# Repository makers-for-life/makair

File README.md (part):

MakAir — Covid-19 Ventilator
=====

Mass-producible open-source Covid-19 ARDS ventilator. Aims at helping hospitals cope with a possible shortage of professional ventilators during the outbreak. Worldwide.

**Makair ventilator is the world's first open-source ventilator tested with success on human patients** with ongoing clinical trials in France.

We are a distributed team of 200+ contributors (engineering, medical, regulatory, etc.), mostly spread through France. Makers, developers, university teachers, researchers and medical teams collaborated on this project. Our testing & assembly operations are located in France.

As to ensure international outreach, we made sure that contents required to build your own MakAir ventilator are available in English. The MakAir project has [a website of its own](https://makair.life/).

If you're new there, please read the explanations below. _Your contributions are much welcome!_

---

**Quick introduction video:**

<p align="center">
  
</p>

---

# Abstract

Roughly, the idea is as follows: as of April 2020 and due to the Covid-19 pandemic, hospitals throughout the world may start lacking mechanical artificial ventilators. We built a pump, and a valve system (controlled by electronics). This way, the breathing cycle can be enforced by proper air routing through the valve system.

Our ventilator is able to handle pressure-controlled breathing, stabilized using a [PID controller](https://en.wikipedia.org/wiki/PID_controller) in the software.

In order to ensure a proper breathing cycle (inhale + exhale), multiple valves need to be connected together to form a circuit. Their motors need to be controlled in harmony so that the air routing between each valve unit is consistent.

This project provides all the parts required to build a good-enough [ARDS](https://en.wikipedia.org/wiki/Acute_respiratory_distress_syndrome) ventilator from mass-produced components. We provide all the required mechanical parts, electronics designs & boards, and firmwares. This ventilator can be 3D-printed and ran on an Arduino board (the maker way), though we **highly advise** that you work with industrial processes as to mold medical-grade plastic parts and assemble the whole ventilator (this would be required for the built ventilator to pass all medical certifications).

We target a per-unit cost well under 500 EUR, which could easily be shrunk down to 200 EUR or even 100 EUR per ventilator given proper economies of scale, as well as choices of cheaper on-the-shelf components (eg. servomotors).

Features include:

- Pressure controlled ventilation (sedated / intubated patients)
- Volume controlled ventilation (sedated / intubated patients)
- BiPap ventilation (non sedated patients with oxygen mask)
- 4 hours battery life
- Medical-grade alarms
- High flow turbine (up to 100 L/min)
- Up to 15 L/min oxygen
- Fault tolerant design
- Designed to be used continuously and intensively during 30 days

MakAir ventilator has been tested by independent researchers and studies found that it can compare with expensive hospital reanimation ventilators (less than 5% error on target pressures and volumes).

Mechanically-speaking, the overall system is composed of sub-components that can be plugged together and wired to form an air circuit, namely:

- **Air pump** (called "Blower");
- **Air pump casing fit** (called "Blower Holder");
- **Valve system** (called "Pressure Valve");
- **Oxygen Mixer valve** (called "Oxygen Mixer");
- **Air filter casing (patient variant)** (called "Patient Filter Box");
- **Air filter casing (machine variant)** (called "Machine Filter Box"; intake + outtake);
- **Connectors** (called "Pneumatic Connectors");
- **Fan support** (called "Fan Holder");

All those components are fitted in box (ie. a casing) that we designed:

- **Housing container** (called "Casing");

---

# Designs

## MakAir Standard (Current Design)

## MakAir Mini (Experimental Design)

---

# ⚠️ Warning Notices

**A few important words before you start:**

1. Though 3D-printing (FDM and SLA) can be used to build your own ventilator — this will definitely not scale well to mass-produce MakAir ventilators, and parts might be brittle or leak air. Please work with proper industrial methods and processes if you want to build your own MakAir ventilators.

2. As ARDS patients are sedated, their breathing cycle is forced by mechanical ventilation, while they are intubated. A failing ventilator (due to bad mechanics, pneumatics or software) could kill the patient (O2 desaturation), or permanently damage their lung alveoli (overpressure). It is critical that any self-built MakAir ventilator is tested against a lung simulator system (eg. [ASL 5000](https://www.ingmarmed.com/product/asl-5000-breathing-simulator/)), and validated by medical experts.

3. Medical-grade plastic should be used to produce ventilators, and any kind of grease or adhesive chemicals must be avoided in the ventilator. The ventilators should be produced in a [cleanroom](https://en.wikipedia.org/wiki/Cleanroom) as to avoid dust & germ contaminations.

4. The pneumatic circuit should be thoroughly tested for leaks and its ability to withstand elevated positive air pressure. Joints should be used where relevant, and medical-grade flexible pipes should be used between components.

5. While the MakAir ventilators produced on-site in France were validated by a medical & engineering board, you should independantly seek validation of the MakAir ventilators that you produce; as your assembly methods or parts may vary with ours.

_MakAir and Makers For Life should not be held resposible — at any time, for harm caused to human life (eg. lung damage or loss of life). By building your own MakAir, you are held responsible for its safety validations & use._

# Projects

As the MakAir ventilator project grew up to be quite large, it is split up in sub-repositories (eg. firmware, PCB designs, etc.).

**Software:**

* **[makair-firmware](https://github.com/makers-for-life/makair-firmware)**: The firmware software source code and builds, that runs on the motherboard;
* **[makair-control-ui](https://github.com/makers-for-life/makair-control-ui)**: The control user interface, that shows realtime graphs of the ventilator while running, on a LCD display;
* **[makair-telemetry](https://github.com/makers-for-life/makair-telemetry)**: The telemetry library (and CLI tool), used as a protocol bridge between the Firmware and Control UI;

**Electronics:**

* **[makair-motherboard](https://github.com/makers-for-life/makair-motherboard)**: The motherboard electronics and PCB design;
* **[makair-boards](https://github.com/makers-for-life/makair-boards)**: Other boards PCB design (smaller control boards);

**Mechanics:**

* **[makair-parts](https://github.com/makers-for-life/makair-parts)**: The mechanical parts that can be 3D-printed and assembled to build the pneumatic circuit;
* **[makair-casing](https://github.com/makers-for-life/makair-casing)**: The MakAir casing which houses all electronics and pneumatics;

**Misc.:**

* **[makair-files](https://github.com/makers-for-life/makair-files)**: Large files, eg. the control UI system image that can be readily flashed and used;
* **[makair-simulator](https://github.com/makers-for-life/makair-simulator)**: The MakAir hardware simulator, that let us run a simulated firmware instance on a computer (for development purposes, ie. not used on ventilator units);
* **[makair-simulator-web](https://github.com/makers-for-life/makair-simulator-web)**: The Web version of the MakAir hardware simulator, that let us run a simulated firmware instance in a Web browser (for development purposes, ie. not used on ventilator units);

# How To Build?

This section aims at introducing you on how to manufacture your own MakAir — _the 3D-printed way_. In other words, we will explain there how to build a DIY MakAir using on-the-shelf parts and 3D printers.

## 1️⃣ Print all the parts

In order to 3D-print your MakAir, please first ensure you have access to a [SLS](https://en.wikipedia.org/wiki/Selective_laser_sintering) 3D printer at best (eg. [HP Multi Jet Fusion](https://www8.hp.com/us/en/printers/3d-printers/products/multi-jet-technology.html)), or otherwise a [SLA](https://en.wikipedia.org/wiki/Stereolithography) printer (eg. [Formlabs Form 3](https://formlabs.com/3d-printers/form-3/)). If you want to use a [FDM](https://en.wikipedia.org/wiki/Fused_filament_fabrication) printer (eg. [MakerBot Method](https://www.makerbot.com/3d-printers/method/)), please note that some precise parts have been optimized for SLA or SLS printing. Some parts may not print well using FDM printers, even on decent hardware.

**👉 To sum up:** at best, use a SLS metal printer, else, use a SLA resin printer. If you do not have access to either of these, you may fallback on a FDM filament printer (using [PLA](https://en.wikipedia.org/wiki/Polylactic_acid) or [ABS](https://en.wikipedia.org/wiki/Acrylonitrile_butadiene_styrene) filaments).

### 1. Parts

You can find a list of all parts that should be 3D-printed, as well as the number of parts that should be printed for each one (pick the last active version for each part):

- 1 x **Blower** — Print [all STL parts](https://github.com/makers-for-life/makair-parts/tree/master/src/blower/printing/stl) using the same printer (SLA or SLS; FDM discouraged; 50 microns minimum);
- 2 x **Pressure Valve** — Print [all STL parts](https://github.com/makers-for-life/makair-parts/tree/master/src/pressure-valve/printing/stl) using the same printer (SLA, SLS or FDM; 200 microns minimum);
- 1 x **Oxygen Mixer** — Print [the STL part](https://github.com/makers-for-life/makair-parts/tree/master/src/oxygen-mixer/printing/stl) (SLA or SLS; FDM discouraged; 100 microns minimum);
- 1 x **Patient Filter Box** — Print [all STL parts](https://github.com/makers-for-life/makair-parts/tree/master/src/patient-filter-box/printing/stl) using the same printer (SLA, SLS or FDM; 100 microns minimum);
- 1 x **Machine Filter Box (Intake)** — Print [all STL parts](https://github.com/makers-for-life/makair-parts/tree/master/src/machine-filter-box/printing/stl) using the same printer, make sure that you pick the proper sub-part (SLA or SLS; FDM discouraged; 100 microns minimum);
- 1 x **Machine Filter Box (Outtake)** — Print [all STL parts](https://github.com/makers-for-life/makair-parts/tree/master/src/machine-filter-box/printing/stl) using the same printer, make sure that you pick the proper sub-part (SLA or SLS; FDM discouraged; 100 microns minimum);
- 1 x **Pneumatic Connectors (Blower)** — Print [the STL part](https://github.com/makers-for-life/makair-parts/tree/master/src/pneumatic-connectors/printing/stl) using the same printer, make sure that you pick the proper sub-part (SLA or SLS; FDM discouraged; 100 microns minimum);
- 1 x **Pneumatic Connectors (O2)** — Print [the STL part](https://github.com/makers-for-life/makair-parts/tree/master/src/pneumatic-connectors/printing/stl) using the same printer, make sure that you pick the proper sub-part (SLA or SLS; FDM discouraged; 100 microns minimum);
- 1 x **Pneumatic Connectors (No Pressure)** — Print [the STL part](https://github.com/makers-for-life/makair-parts/tree/master/src/pneumatic-connectors/printing/stl) using the same printer, make sure that you pick the proper sub-part (SLA or SLS; FDM discouraged; 100 microns minimum);
- 1 x **Pneumatic Connectors (Pressure)** — Print [the STL part](https://github.com/makers-for-life/makair-parts/tree/master/src/pneumatic-connectors/printing/stl) using the same printer, make sure that you pick the proper sub-part (SLA or SLS; FDM discouraged; 100 microns minimum);

If you are using your own proprietary blower — _in addition to the parts above_ — please adjust the [Blower Holder](https://github.com/makers-for-life/makair-parts/tree/master/src/blower-holder) CAD model and print it as well (this one prints well using a FDM printer at worst).

### 2. Casing

Now that you got all parts printed, you may assemble them in the MakAir casing box. We recommend that you build the casing using laser-cut acrylic panels. You may find the casing CAD model for [Fusion 360](https://github.com/makers-for-life/makair-casing/tree/master/src/fusion) or as a [STEP file](https://github.com/makers-for-life/makair-casing/tree/master/src/step).

_Please ensure that you cut your acrylic panels using the same sizes than stated on our models; as those sizes are optimized to contain all required parts and electronics in the minimum amount of space._

## 2️⃣ Setup the electronics

Electronics are comprised of two parts: the firmware controller board (typically, an Arduino), and the "raw" PCB electronics (LCD, interface buttons, alarm beeper, etc.). Those parts make up the motherboard, on the top of which a rigid panel is mounted, and user instructions are printed (eg. control button bindings).

### 1. Motherboard

The motherboard electronic schematics and wiring diagrams [can be found there](https://github.com/makers-for-life/makair-motherboard/tree/master/src/schematics). Please pick the last version available.

👋 _If you need help on this step, you may [open an issue](https://github.com/makers-for-life/makair-motherboard/issues/new)._

### 2. Smaller Boards

The smaller boards electronic schematics and wiring diagrams [can be found there](https://github.com/makers-for-life/makair-boards/tree/master/src/schematics). Please pick the last version available. Those boards are used eg. to control the pinch valve motor or Raspberry Pi hardware clock.

👋 _If you need help on this step, you may [open an issue](https://github.com/makers-for-life/makair-boards/issues/new)._

### 3. Control Unit Screen

The control unit is made of a [Raspberry Pi 4](https://www.raspberrypi.org/products/raspberry-pi-4-model-b/) computer, plugged to a [Raspberry Pi Touch Display](https://www.raspberrypi.org/products/raspberry-pi-touch-display/).

👋 _If you need help on this step, you may [open an issue](https://github.com/makers-for-life/makair-control-ui/issues/new)._

## 3️⃣ Flash the firmware

### 1. Ventilator Firmware

Now that both mechanical parts and electronics are ready, you may flash the latest MakAir firmware binary on your firmware controller board (Arduino, ST Nucleo, or other).

Firmware release binaries are available for download on our [releases page](https://github.com/makers-for-life/makair-firmware/releases).

👋 _If you need help on this step, you may [open an issue](https://github.com/makers-for-life/makair-firmware/issues/new)._

### 2. Control Unit Runtime

The Control Unit should be built and ran on the Raspberry Pi 4 using instructions available on the [Control Unit](https://github.com/makers-for-life/makair-control-ui) documentation. You should flash the system image readily available in the [Files](https://github.com/makers-for-life/makair-files) repository.

👋 _If you need help on this step, you may [open an issue](https://github.com/makers-for-life/makair-control-ui/issues/new)._

# Schemes

## Pneumatic Circuit Scheme

_(design by [Valerian Saliou](https://github.com/valeriansaliou))_

## Casing Layout

### Top Part: Electronics (Power & Controllers)

_(design by Arthur Dagard; drawing by [Valerian Saliou](https://github.com/valeriansaliou); remake by [Lāsma Fedotova](https://github.com/lasmafedotova))_

### Bottom Part: Pneumatics

_(design by Arthur Dagard; drawing by [Valerian Saliou](https://github.com/valeriansaliou); remake by [Lāsma Fedotova](https://github.com/lasmafedotova))_

# Article Series

A series of explanatory articles have been written on the MakAir story, with the goal of making it easier for teams in the future to start their own ventilator project:

* 1️⃣ [MakAir Series: The Inception of an Open-Source Ventilator Project](https://journal.valeriansaliou.name/makair-series-the-inception-of-an-open-source-ventilator-project/)
* 2️⃣ [MakAir Series: How to Ventilate a Human Patient 101](https://journal.valeriansaliou.name/makair-series-how-to-ventilate-a-human-patient-101/)
* 3️⃣ [MakAir Series: The Building Blocks of a Mechanical Ventilator](https://journal.valeriansaliou.name/makair-series-the-building-blocks-of-a-mechanical-ventilator/)
* 4️⃣ [MakAir Series: Engineering Focus on Ventilator Pneumatics](https://journal.valeriansaliou.name/makair-series-engineering-focus-on-ventilator-pneumatics/)
* 5️⃣ [MakAir Series: Engineering Focus on Ventilator Electronics](https://journal.valeriansaliou.name/makair-series-engineering-focus-on-ventilator-electronics/)
* 6️⃣ [MakAir Series: Engineering Focus on Ventilator Software](https://journal.valeriansaliou.name/makair-series-engineering-focus-on-ventilator-software/)

# News & Contact

## Updates

* Live updates on Telegram: [join "Newsroom MakAir (Covid-19 Ventilator)"](https://t.me/joinchat/AAAAAE_99-k7pKZur-GXCQ)
* YouTube channel: [view "MakAir" on YouTube](https://www.youtube.com/channel/UCcf_3KXjeJSMz39J6gsyTSg)
* Coordination on Slack: [request to join "Makers For Life"](https://github.com/makers-for-life/makair/issues/new) (open an issue)

## Contacts

* Open-source & questions: [please open an issue on GitHub](https://github.com/makers-for-life/makair/issues/new)
* Press contacts: [Grégory Thibord](https://twitter.com/thibord) ([email](mailto:gregory.thibord@lepalace.work))
* Medical contacts: [Pierre Antoine Gourraud](http://www.itun.nantes.inserm.fr/Team-5/Pierre-Antoine-Gourraud) ([email](mailto:pierre-antoine.gourraud@univ-nantes.fr))
* Industry relations: [Quentin Adam](http://waxzce.org/) ([email](mailto:quentin.adam@clever-cloud.com))
* Engineering contact (mechanics): [Valerian Saliou](https://valeriansaliou.name/) ([email](mailto:valerian@valeriansaliou.name))
* Engineering contact (software): [David Sferruzza](https://david.sferruzza.fr/) ([email](mailto:david.sferruzza@gmail.com))
* Engineering contact (electronics): Vincent Le Cunff ([email](mailto:v.lecunf@gmail.com))

# Sponsors & Contributors

This project would not have been possible without the support of those companies and organizations, which have put human, real estate and/or financial resources at work on the project:

* [Clever Cloud](https://www.clever-cloud.com/) (founding team)
* [Crisp](https://crisp.chat/) (founding team)
* [Cooprint](https://cooprint.fr/) (CAD)
* [SenX](https://senx.io/) (electronics)
* [Tronico](https://www.tronico-alcen.com/) (PCB design)
* [Renault Group](https://www.renault.fr/) (manufacturing)
* [SEB Group](https://www.groupeseb.com/) (manufacturing)
* [Le Palace Nantes](https://lepalace.work/) (team offices)
* [Parrot](https://www.parrot.com/) (hardware provider)
* [STMicroelectronics](https://www.st.com/) (hardware provider)
* [Diabeloop](https://www.diabeloop.com/) (regulatory help)
* [Legrand](https://www.legrand.fr/) (hardware provider)
* [RTsys](https://rtsys.eu/) (engineering provider)

We are supported by public entities as well, namely:

* [Defence Innovation Agency](https://www.defense.gouv.fr/) (Ministry of Armed Forces of France)
* [CEA](http://www.cea.fr/) (France)
* [CHU of Nantes](https://www.chu-nantes.fr/) (France)
* [University of Nantes](https://www.univ-nantes.fr/) (France)
* [City of Nantes](https://metropole.nantes.fr/) (France)
* [Region of Auvergne-Rhône-Alpes](https://www.auvergnerhonealpes.fr/) (France)

Adding to that, 200+ individual members of the project who contributed to technical, legal, medical and press subjects (and more).

# Research Papers

* [Can Open Source Hardware Mechanical Ventilator initiatives help cope with the COVID-19 health crisis](https://www.sciencedirect.com/science/article/pii/S2468067220300596) (English)
* [MakAir, a COVID-19-born ventilation machine, combining 3D printing design, digital control and open innovation](https://www.sciencedirect.com/science/article/pii/S1279847920301129) (French)

# Press Coverage

## 📺 TV

* [France 3, 21st April 2020](https://www.youtube.com/watch?v=M3QLCvUyIII) (French-speaking)
* [TF1, 26th April 2020](https://www.youtube.com/watch?v=2X157RLbRIA) (French-speaking)

## 🗞 Newspapers

* [Makery, 23th July 2020](https://www.makery.info/en/2020/07/23/quentin-adam-lopen-source-medical-est-une-idee-qui-fera-son-chemin/) (English)
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
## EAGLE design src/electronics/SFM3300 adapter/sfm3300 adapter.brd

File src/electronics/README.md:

# Electronics

| Electronics | Repository |
| --- | --- |
| Motherboard | [makair-motherboard](https://github.com/makers-for-life/makair-motherboard) |
| Boards | [makair-boards](https://github.com/makers-for-life/makair-boards) |

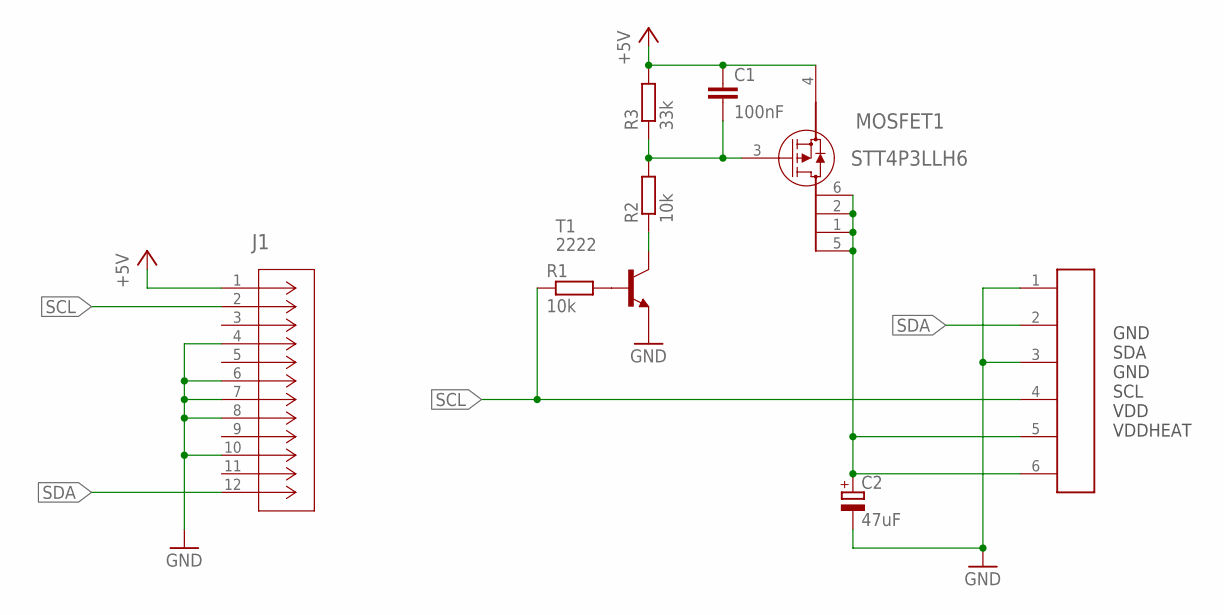
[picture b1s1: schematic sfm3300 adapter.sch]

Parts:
C1: 100nF; C0603
C2: 47uF; SMC_A
J1: 1-188275-2; CONN_1-188275-2_TYC
MOSFET1: STT4P3LLH6; SOT23-6L_STM
R1, R2: 10k; R0603
R3: 33k; R0603
T1: 2222; SOT23-BEC
U$1: SPRING6; SPRING-6

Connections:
+5V: C1.1, J1.1, MOSFET1.4, R3.2
GND: C2.-, J1.4, J1.6, J1.7, J1.8, J1.10, T1.E, U$1.1, U$1.3
unnamed: R1.2, T1.B
unnamed: C1.2, MOSFET1.3, R2.2, R3.1
unnamed: R2.1, T1.C
unnamed: C2.+, MOSFET1.1, MOSFET1.2, MOSFET1.5, MOSFET1.6, U$1.5, U$1.6
SCL: J1.2, R1.1, U$1.4
SDA: J1.12, U$1.2

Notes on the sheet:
GND SDA GND SCL VDD VDDHEAT

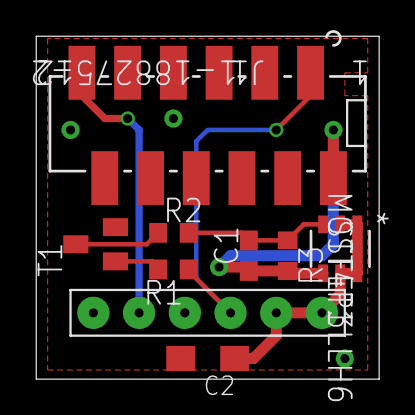
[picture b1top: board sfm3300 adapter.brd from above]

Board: 2 copper layers, 19.1 x 19.0 mm, 9 parts (0 on the bottom side), 8 nets.

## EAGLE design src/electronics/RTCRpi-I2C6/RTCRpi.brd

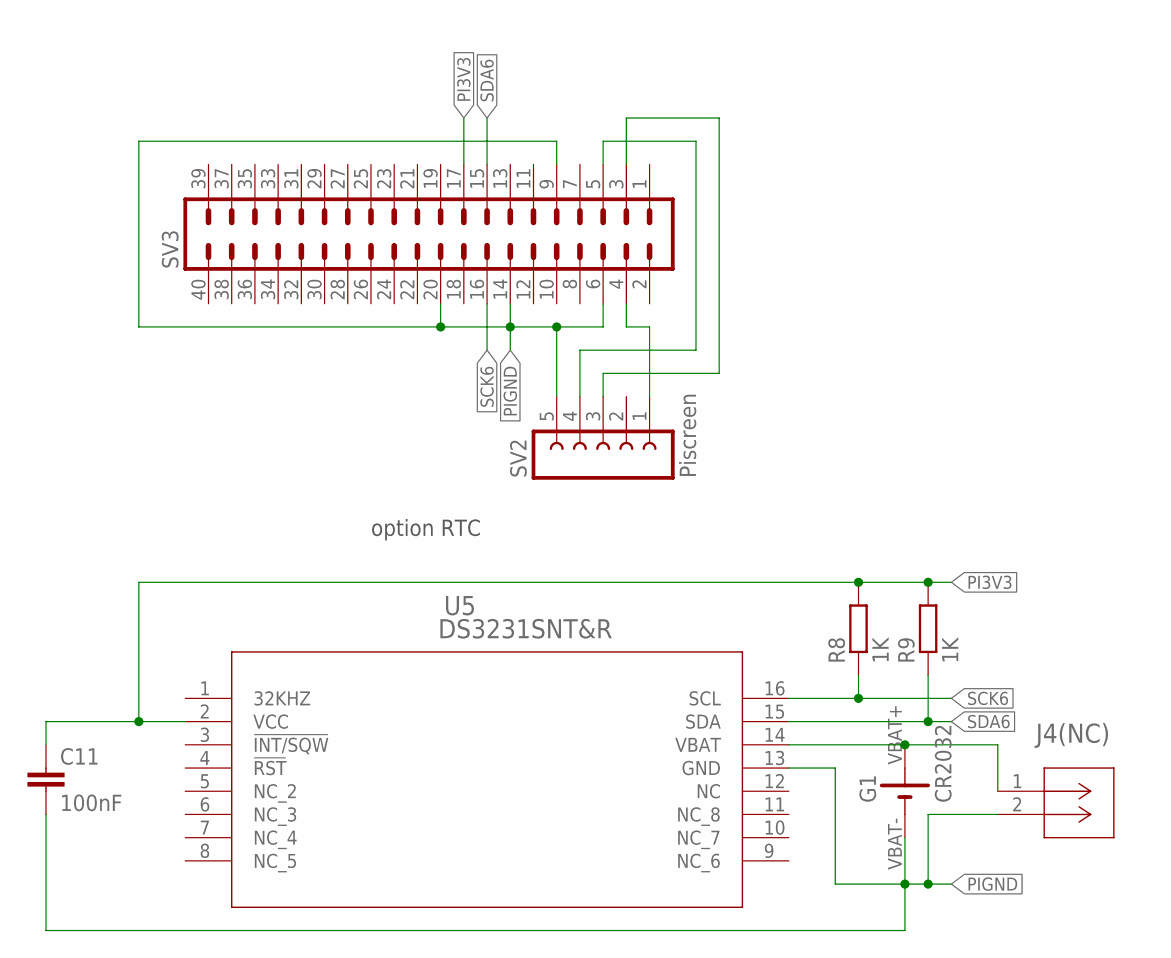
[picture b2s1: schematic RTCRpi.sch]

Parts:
C11: 100nF; C0603K
G1: CR2032
J4(NC): B2B-XH-A(LF)(SN); CONN_B2B-XH-A(LF)(SN)_JST
R8, R9: 1K; R0805
SV2: Piscreen; FE05-1
SV3: MA20-2
U5: DS3231SNT&R; 21-0042B_16_MXM

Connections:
unnamed: SV2.1, SV3.4
unnamed: SV2.4, SV3.5
unnamed: SV2.3, SV3.3
PI3V3: C11.1, R8.2, R9.2, SV3.17, U5.2 (VCC)
PIGND: C11.2, G1.VBAT- (-), J4(NC).2, SV2.5, SV3.6, SV3.9, SV3.14, SV3.20, U5.13 (GND)
SCK6: R8.1, SV3.16, U5.16 (SCL)
SDA6: R9.1, SV3.15, U5.15 (SDA)
VBAT+: G1.VBAT+ (+), J4(NC).1, U5.14 (VBAT)

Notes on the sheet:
option RTC

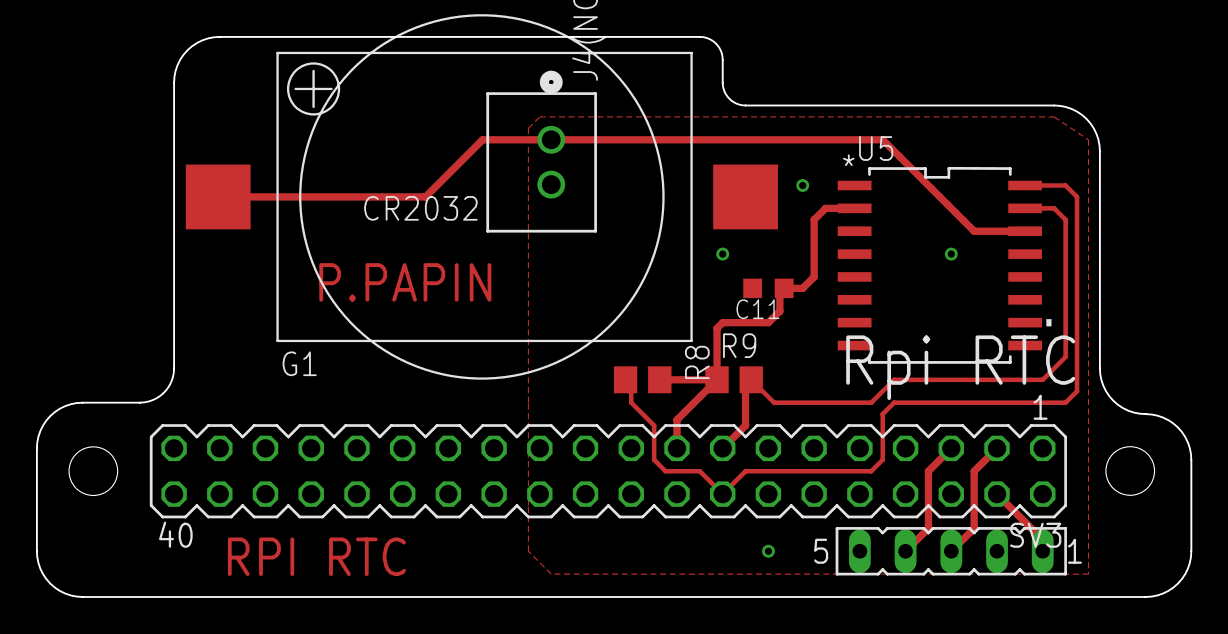
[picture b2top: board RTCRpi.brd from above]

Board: 2 copper layers, 64.1 x 31.1 mm, 8 parts (0 on the bottom side), 8 nets.

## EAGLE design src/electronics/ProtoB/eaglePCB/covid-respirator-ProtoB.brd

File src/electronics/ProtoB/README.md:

# Proto B

2020/03/25

## Requirements

- simpler calibration process: no amplification.
- only one 12V input : allow battery
- low noise : clean separation of power supply of the sensor, no ground loops, use of external ADC reference.
- able to drive the blower
- powerfull alarm buzzer
- no surface mount components
- components available and in stock in both Farnell and Radiospares.
- safety: not mandatory to have 60601, 60950-1 is enough

MHRA specifications: [link](https://assets.publishing.service.gov.uk/government/uploads/system/uploads/attachment_data/file/874279/RMVS001_Rapidly_Manufactured_Ventilator_Specification__PDF.pdf). 

## Schematic

See [pdf file](./covid-respirator-ProtoB.pdf)

## Bill Of Material

### Power supply

13.8v output to ensure a slow floating charge of a 12V lead battery:
- RS: 740-5001
- RS: 161-8267  (10A version, dangerous for battery)

### Battery
Lead battery, 7Ah.
- RS: 537-5488

### Fuse
A 7Ah 12V lead battery has enough power to harm anyone. A fuse is necessary.
10A value needs to be confirmed after blower motor will be choosen.

10A (slow fuse).
- RS: 563-429

### Fuse holder:
- RS  344-5642
- Farnell 1154859

### Sensor: 

Medical specification : `Plateau pressure should be adjusted to achieve volume and be limited
to 35 cmH2O by default. It is acceptable if an option to increase this to
70 cmH2O in exceptional circumstances is provided`
> The 1psi (69mbar, 7kPa, 703mmH2O, 27inchH2O) range is perfect.

See this comparison table of different sensors with availability around major suppliers : [google doc link](https://docs.google.com/spreadsheets/d/1qR-S2XOJmOITaHZXnXCGtpi7E2upIdV9PGvASUbvRIo/edit?usp=sharing)

[MPXV5010DP](https://www.nxp.com/docs/en/data-sheet/MPX5010.pdf) : Good range, 5% accuracy (not so good), **available for mass production**. Easy to read analog output.

[NXP MPX5010DP](https://www.nxp.com/docs/en/data-sheet/MPX5010.pdf) : Not a very good accuracy, easy to read analog output.
- RS: 719-1080
- Farnell: 1555605

[Honeywell HSCSAAN001PDAA5](https://sensing.honeywell.com/honeywell-sensing-trustability-hsc-series-high-accuracy-board-mount-pressure-sensors-50099148-a-en.pdf) : Best one. Accurate, easy to read analog output. **But only available on Farnell**.
- Farnell : 1823226

### Power Supply:
Battery size will be choosen once the blower will choosen. Any 12V lead battery can do the job, ~5Ah minimum. 

### Mains supply:
This is a battery charger. It must be able to charge the battery and keep it floating at around 13.6Volts. A good 13.8 V fixed power supply can do the job.

### Blower driver:
Arduino can drive the blower through a robust low side mosfet :

VNP35N07-E
- RS: 809-1310
- Farnell : 1739428

Blower motor may be a RC motor controlled by the arduino. **TO BE DEFINED**.

### Battery voltage feedback:
The arduino is able to monitor battery voltage and raise alarm if the voltage goes under 12.7V (mains loss). This is a simple voltage divider.

### Arduino and servo power supply:
Buck regulator that can support a wide input range:
- RS: 144-6290
- Farnell : 2760747
This could be replaced by another one easily (5V 1A output)

### Buzzer:
Powerfull Buzzer, fixed tone, electronics integrated. Just need to power it, directly with 12V supply. BC548 can be replaced by any NPN transistor that support 30V/100mA.

KXG1212CL
- RS: 771-6960
- Farnell : 2215083

BC548
- RS : 796-9713
- Farnell : 2453793

Note : R6 may be connected to +12V to power the alarm if the arduino fails. Monitoring Arduino with an external watchdog need to be discussed in ProtoC.

### Sensor supply:
In order to minimize the measure noise, the sensor has a dedicated linear regulator (7805), a bit of power filtering, a little low pass filter (R5 C4).

> The ground must come from the arduino, not from other part of the circuit.

> The sensor circuit board and power supply must be isolated from other components, and really close to the arduino. Ideally, less than 4cm of 1mm² wire.

L7805CV-DG
- RS: 793-1346
- Farnell: 2849718
47uF/25V
- RS 807-3324 
- Farnell 2917904
10uF/16V
- RS 862-3083 
- Farnell 9451692
100nF/50V
- RS 133-5716 
- Farnell 2507749

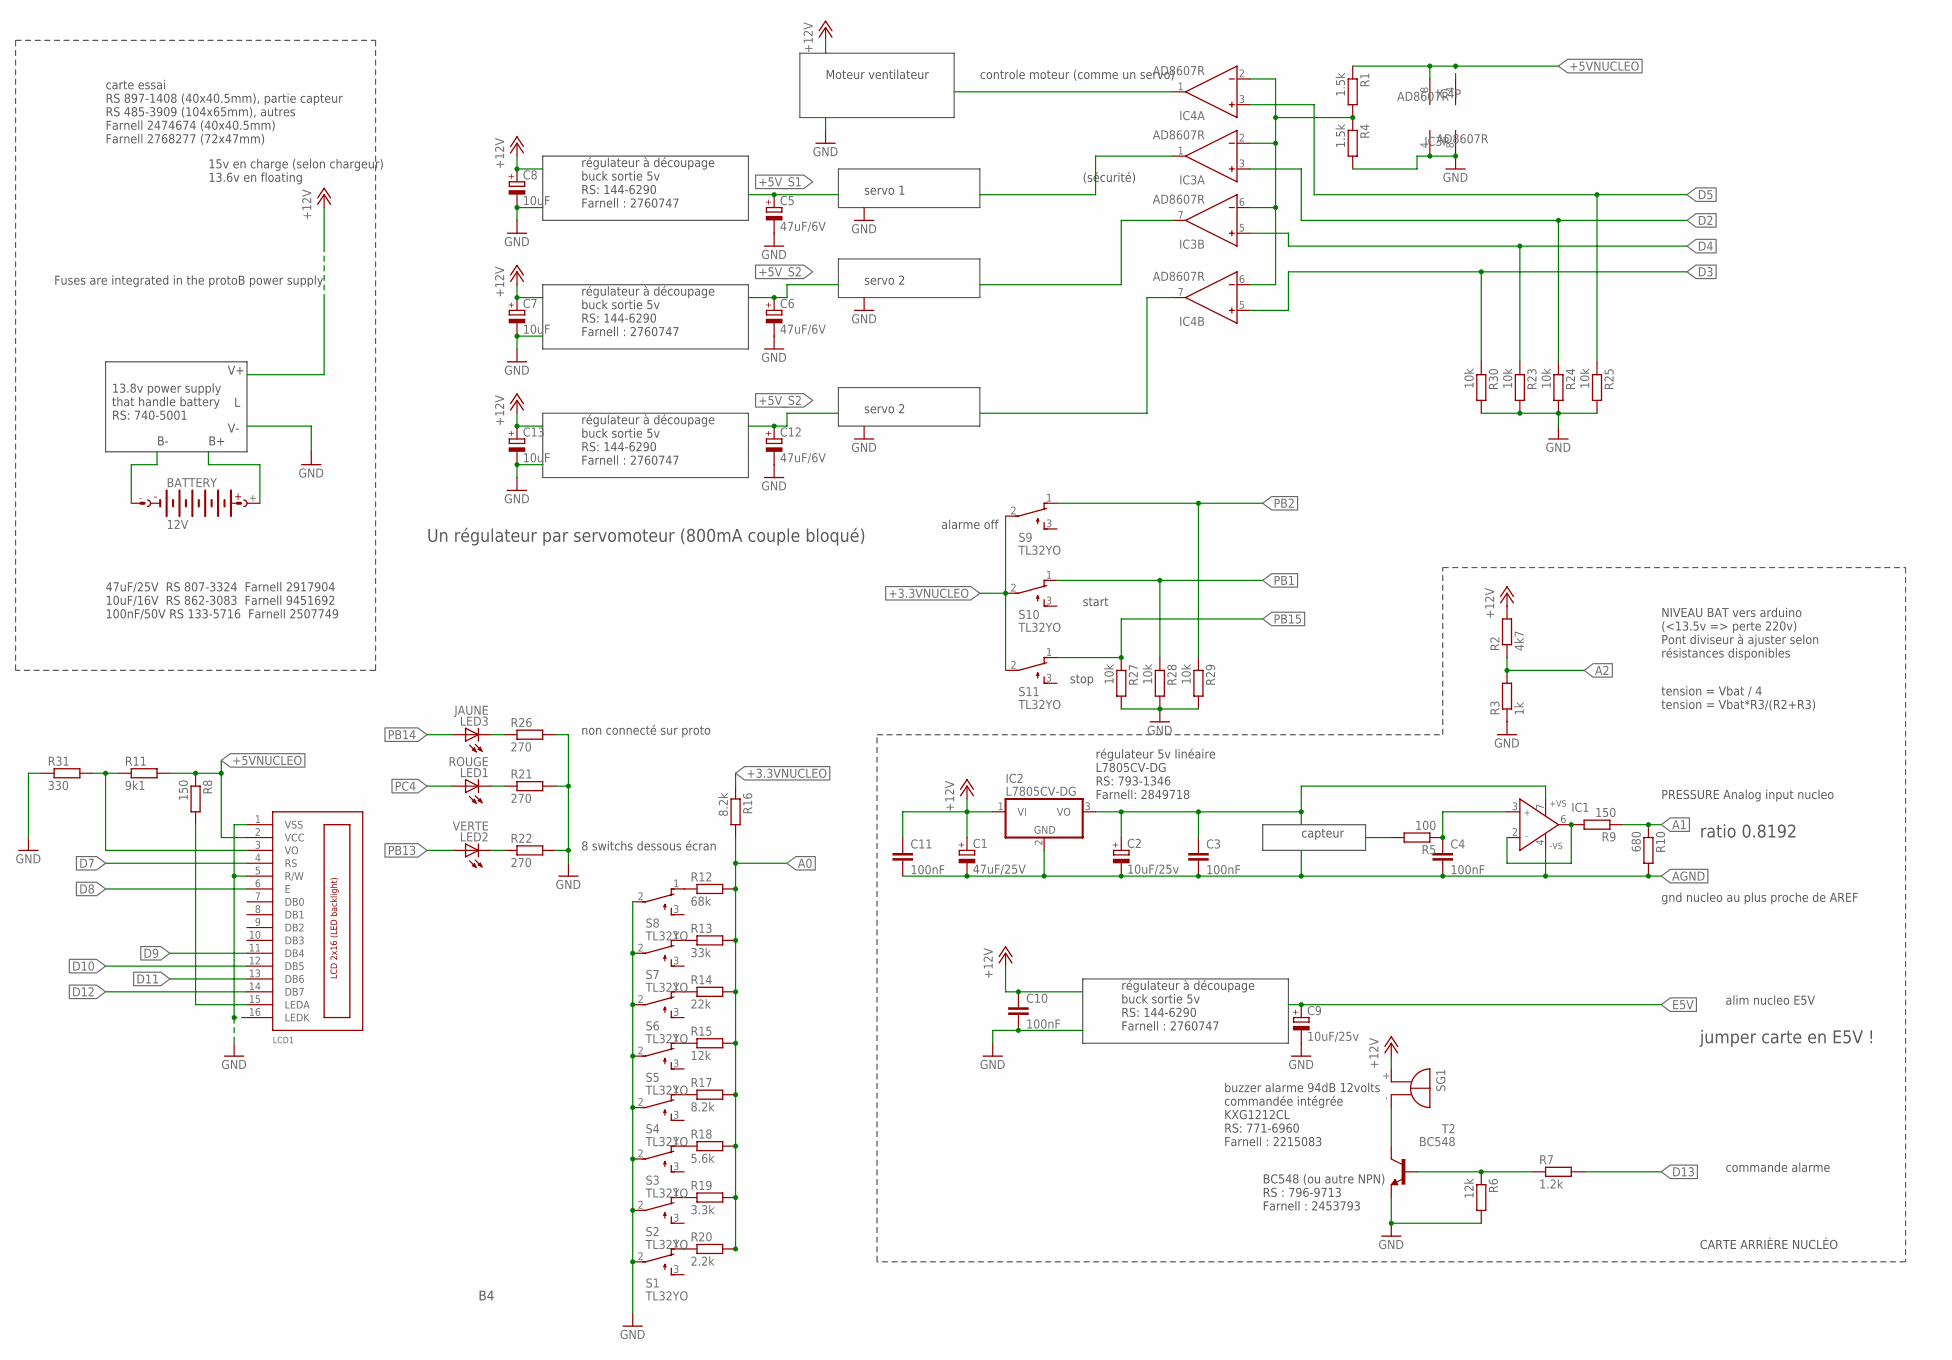
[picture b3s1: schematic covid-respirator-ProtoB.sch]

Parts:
BATTERY: 12V; AB9V
C1: 47uF/25V; 150CLZ-1010
C2, C9: 10uF/25v; 150CLZ-1010
C3, C4, C10, C11: 100nF; C050-050X075
C5, C6, C12: 47uF/6V; 150CLZ-1010
C7, C8, C13: 10uF; 150CLZ-1010
IC1: AD825R; SO8
IC2: L7805CV-DG; TO220H
IC3, IC4: AD8607R; SO8
LCD1: LCD_2X16_SIL; HY-1602F
LED1: ROUGE; LED3MM
LED2: VERTE; LED3MM
LED3: JAUNE; LED3MM
R1, R4: 1.5k; 0207/10
R2: 4k7; 0207/10
R3: 1k; 0207/10
R5: 100; 0207/10
R6, R15: 12k; 0207/10
R7: 1.2k; 0207/10
R8, R9: 150; 0207/10
R10: 680; 0207/10
R11: 9k1; 0207/10
R12: 68k; 0207/10
R13: 33k; 0207/10
R14: 22k; 0207/10
R16, R17: 8.2k; 0207/10
R18: 5.6k; 0207/10
R19: 3.3k; 0207/10
R20: 2.2k; 0207/10
R21, R22, R26: 270; 0207/10
R23, R24, R25, R27, R28, R29, R30: 10k; 0207/10
R31: 330; 0207/10
S1, S2, S3, S4, S5, S6, S7, S8, S9, S10, S11: TL32YO; TL3XYO
SG1: F/EB20P
T2: BC548; TO92-CBE

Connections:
6546876: C4.1, IC1.3 (IN+), R5.1
+3.3VNUCLEO: R16.1, S9.2, S10.2, S11.2
+5VNUCLEO: IC3.4 (V-), IC4.8 (V+), LCD1.2 (VCC), R1.1, R8.1, R11.2
+5V_S1: C5.+
+5V_S2: C6.+, C12.+
+12V: C1.+, C7.+, C8.+, C10.1, C11.1, C13.+, IC2.1 (VI), R2.2, SG1.+
A0: R12.2, R13.2, R14.2, R15.2, R16.2, R17.2, R18.2, R19.2, R20.2
A1: R9.1, R10.1
A2: R2.1, R3.2
AGND: C1.-, C2.-, C3.2, C4.2, C11.2, IC1.4 (-VS), IC2.2 (GND), R10.2
AREF: C2.+, C3.1, IC1.7 (+VS), IC2.3 (VO)
D2: IC3.3 (IN+), R24.1
D3: IC4.5 (IN+), R30.1
D4: IC3.5 (IN+), R23.1
D5: IC4.3 (IN+), R25.1
D7: LCD1.4 (RS)
D8: LCD1.6 (E)
D9: LCD1.11 (DB4)
D10: LCD1.12 (DB5)
D11: LCD1.13 (DB6)
D12: LCD1.14 (DB7)
D13: R7.2
E5V: C9.+
GND: C5.-, C6.-, C7.-, C8.-, C9.-, C10.2, C12.-, C13.-, IC3.8 (V+), IC4.4 (V-), LCD1.1 (VSS), LCD1.5 (R/W), LCD1.16 (LEDK), R3.1, R4.2, R6.2, R21.2, R22.2, R23.2, R24.2, R25.2, R26.2, R27.2, R28.2, R29.2, R30.2, R31.1, S1.2, S2.2, S3.2, S4.2, S5.2, S6.2, S7.2, S8.2, T2.E
unnamed: IC3.2 (IN-), IC3.6 (IN-), IC4.2 (IN-), IC4.6 (IN-), R1.2, R4.1
unnamed: LCD1.15 (LEDA), R8.2
unnamed: IC1.2 (IN-), IC1.6 (OUT), R9.2
unnamed: LCD1.3 (VO), R11.1, R31.2
unnamed: R12.1, S8.1 (O)
unnamed: SG1.-, T2.C
unnamed: R6.1, R7.1, T2.B
unnamed: R13.1, S7.1 (O)
unnamed: R14.1, S6.1 (O)
unnamed: R15.1, S5.1 (O)
unnamed: R17.1, S4.1 (O)
unnamed: R18.1, S3.1 (O)
unnamed: R19.1, S2.1 (O)
unnamed: R20.1, S1.1 (O)
unnamed: LED3.K (C), R26.1
unnamed: LED1.K (C), R21.1
unnamed: LED2.K (C), R22.1
PB1: R28.1, S10.1 (O)
PB2: R29.1, S9.1 (O)
PB13: LED2.A
PB14: LED3.A
PB15: R27.1, S11.1 (O)
PC4: LED1.A

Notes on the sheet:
Moteur ventilateur
controle moteur (comme un servo)
(sécurité)
NIVEAU BAT vers arduino (<13.5v => perte 220v) Pont diviseur à ajuster selon résistances disponibles
tension = Vbat / 4 tension = Vbat*R3/(R2+R3)
15v en charge (selon chargeur) 13.6v en floating
capteur
PRESSURE Analog input nucleo
gnd nucleo au plus proche de AREF
régulateur à découpage buck sortie 5v RS: 144-6290 Farnell : 2760747
alim nucleo E5V
régulateur 5v linéaire L7805CV-DG RS: 793-1346 Farnell: 2849718
buzzer alarme 94dB 12volts commandée intégrée KXG1212CL RS: 771-6960 Farnell : 2215083
BC548 (ou autre NPN) RS : 796-9713 Farnell : 2453793
CARTE ARRIÈRE NUCLÉO
carte essai RS 897-1408 (40x40.5mm), partie capteur RS 485-3909 (104x65mm), autres Farnell 2474674 (40x40.5mm) Farnell 2768277 (72x47mm)
47uF/25V RS 807-3324 Farnell 2917904 10uF/16V RS 862-3083 Farnell 9451692 100nF/50V RS 133-5716 Farnell 2507749
13.8v power supply that handle battery RS: 740-5001
Un régulateur par servomoteur (800mA couple bloqué)
ratio 0.8192
jumper carte en E5V !
commande alarme
Fuses are integrated in the protoB power supply
servo 1
servo 2
8 switchs dessous écran
non connecté sur proto
alarme off
start
stop

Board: 2 copper layers, 66 parts (0 on the bottom side), 35 nets, no tracks yet.

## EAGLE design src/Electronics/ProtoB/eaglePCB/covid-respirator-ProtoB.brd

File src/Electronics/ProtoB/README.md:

# Proto B

2020/03/22

## Requirements

- simpler calibration process: no amplification.
- only one 12V input : allow battery
- low noise : clean separation of power supply of the sensor, no ground loops, use of external ADC reference.
- able to drive the blower
- powerfull alarm buzzer
- no surface mount components
- components available and in stock in both Farnell and Radiospares.
- safety: not mandatory to have 60601, 60950-1 is enough

## Schematic

See [pdf file](./covid-respirator-ProtoB.pdf)

## Bill Of Material

### Power supply

13.8v output to ensure a slow floating charge of a 12V lead battery:
- RS: 740-5001
- RS: 161-8267  (10A version, dangerous for battery)

### Battery
Lead battery, 7Ah.
- RS: 537-5488

### Fuse
A 7Ah 12V lead battery has enough power to harm anyone. A fuse is necessary.
10A value needs to be confirmed after blower motor will be choosen.

10A (slow fuse).
- RS: 563-429

### Fuse holder:
- RS  344-5642
- Farnell 1154859

### Sensor: 

Medical specification : `Plateau pressure should be adjusted to achieve volume and be limited
to 35 cmH2O by default. It is acceptable if an option to increase this to
70 cmH2O in exceptional circumstances is provided`
> The 1psi (69mbar, 7kPa, 703mmH2O, 27inchH2O) range is perfect.

See this comparison table of different sensors with availability around major suppliers : [google doc link](https://docs.google.com/spreadsheets/d/1qR-S2XOJmOITaHZXnXCGtpi7E2upIdV9PGvASUbvRIo/edit?usp=sharing)

[MPXV5010DP](https://www.nxp.com/docs/en/data-sheet/MPX5010.pdf) : Good range, 5% accuracy (not so good), **available for mass production**. Easy to read analog output.

[NXP MPX5010DP](https://www.nxp.com/docs/en/data-sheet/MPX5010.pdf) : Not a very good accuracy, easy to read analog output.
- RS: 719-1080
- Farnell: 1555605

[Honeywell HSCSAAN001PDAA5](https://sensing.honeywell.com/honeywell-sensing-trustability-hsc-series-high-accuracy-board-mount-pressure-sensors-50099148-a-en.pdf) : Best one. Accurate, easy to read analog output. **But only available on Farnell**.
- Farnell : 1823226

### Power Supply:
Battery size will be choosen once the blower will choosen. Any 12V lead battery can do the job, ~5Ah minimum. 

### Mains supply:
This is a battery charger. It must be able to charge the battery and keep it floating at around 13.6Volts. A good 13.8 V fixed power supply can do the job.

### Blower driver:
Arduino can drive the blower through a robust low side mosfet :

VNP35N07-E
- RS: 809-1310
- Farnell : 1739428

Blower motor may be a RC motor controlled by the arduino. **TO BE DEFINED**.

### Battery voltage feedback:
The arduino is able to monitor battery voltage and raise alarm if the voltage goes under 12.7V (mains loss). This is a simple voltage divider.

### Arduino and servo power supply:
Buck regulator that can support a wide input range:
- RS: 144-6290
- Farnell : 2760747
This could be replaced by another one easily (5V 1A output)

### Buzzer:
Powerfull Buzzer, fixed tone, electronics integrated. Just need to power it, directly with 12V supply. BC548 can be replaced by any NPN transistor that support 30V/100mA.

KXG1212CL
- RS: 771-6960
- Farnell : 2215083

BC548
- RS : 796-9713
- Farnell : 2453793

Note : R6 may be connected to +12V to power the alarm if the arduino fails. Monitoring Arduino with an external watchdog need to be discussed in ProtoC.

### Sensor supply:
In order to minimize the measure noise, the sensor has a dedicated linear regulator (7805), a bit of power filtering, a little low pass filter (R5 C4).

> The ground must come from the arduino, not from other part of the circuit.

> The sensor circuit board and power supply must be isolated from other components, and really close to the arduino. Ideally, less than 4cm of 1mm² wire.

L7805CV-DG
- RS: 793-1346
- Farnell: 2849718
47uF/25V
- RS 807-3324 
- Farnell 2917904
10uF/16V
- RS 862-3083 
- Farnell 9451692
100nF/50V
- RS 133-5716 
- Farnell 2507749

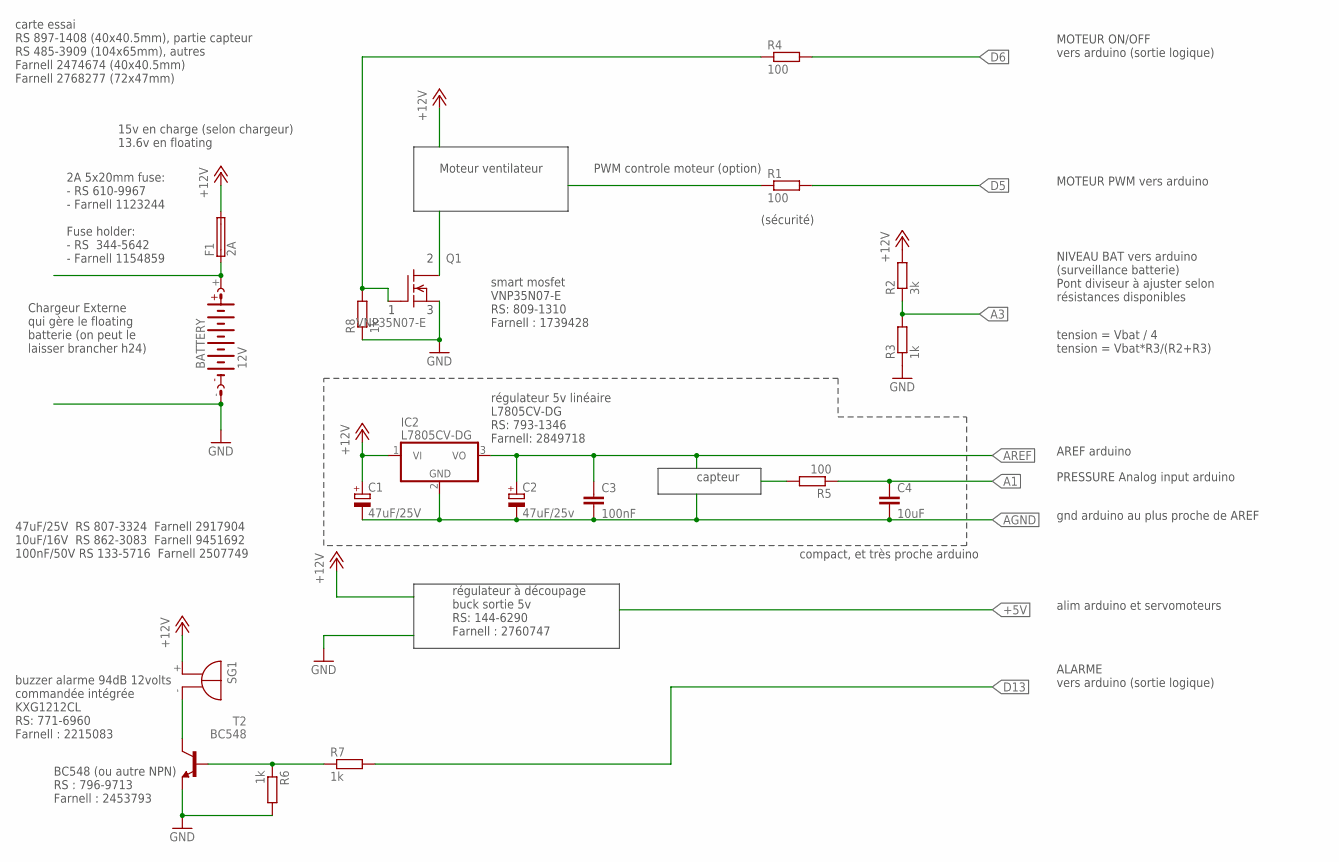
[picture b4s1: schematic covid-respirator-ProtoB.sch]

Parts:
BATTERY: 12V; AB9V
C1: 47uF/25V; 150CLZ-1010
C2: 47uF/25v; 150CLZ-1010
C3: 100nF; C050-050X075
C4: 10uF; C050-050X075
F1: 2A; 19560
IC2: L7805CV-DG; TO220H
Q1: VNP35N07-E; TO220
R1, R4, R5: 100; 0207/10
R2: 3k; 0207/10
R3, R6, R7, R8: 1k; 0207/10
SG1: F/EB20P
T2: BC548; TO92-CBE

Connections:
+12V: C1.+, F1.2, IC2.1 (VI), R2.2, SG1.+
A1: C4.1, R5.1
A3: R2.1, R3.2
AGND: C1.-, C2.-, C3.2, C4.2, IC2.2 (GND)
AREF: C2.+, C3.1, IC2.3 (VO)
D5: R1.2
D6: R4.2
D13: R7.2
GND: BATTERY.-, Q1.3 (S), R3.1, R6.2, R8.1, T2.E
unnamed: Q1.1 (G), R4.1, R8.2
unnamed: SG1.-, T2.C
unnamed: R6.1, R7.1, T2.B
unnamed: BATTERY.+, F1.1

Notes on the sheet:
Chargeur Externe qui gère le floating batterie (on peut le laisser brancher h24)
Moteur ventilateur
PWM controle moteur (option)
(sécurité)
MOTEUR PWM vers arduino
NIVEAU BAT vers arduino (surveillance batterie) Pont diviseur à ajuster selon résistances disponibles
tension = Vbat / 4 tension = Vbat*R3/(R2+R3)
15v en charge (selon chargeur) 13.6v en floating
MOTEUR ON/OFF vers arduino (sortie logique)
capteur
AREF arduino
PRESSURE Analog input arduino
gnd arduino au plus proche de AREF
régulateur à découpage buck sortie 5v RS: 144-6290 Farnell : 2760747
alim arduino et servomoteurs
smart mosfet VNP35N07-E RS: 809-1310 Farnell : 1739428
régulateur 5v linéaire L7805CV-DG RS: 793-1346 Farnell: 2849718
buzzer alarme 94dB 12volts commandée intégrée KXG1212CL RS: 771-6960 Farnell : 2215083
ALARME vers arduino (sortie logique)
BC548 (ou autre NPN) RS : 796-9713 Farnell : 2453793
compact, et très proche arduino
carte essai RS 897-1408 (40x40.5mm), partie capteur RS 485-3909 (104x65mm), autres Farnell 2474674 (40x40.5mm) Farnell 2768277 (72x47mm)
47uF/25V RS 807-3324 Farnell 2917904 10uF/16V RS 862-3083 Farnell 9451692 100nF/50V RS 133-5716 Farnell 2507749
2A 5x20mm fuse: - RS 610-9967 - Farnell 1123244 Fuse holder: - RS 344-5642 - Farnell 1154859

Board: 2 copper layers, 18 parts (0 on the bottom side), 10 nets, no tracks yet.

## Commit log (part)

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2020-04-23 Bump sponsors
2020-04-23 Patch LUT v1
2020-04-23 Telemetry library added to README + more Control UI code refactoring doen
2020-04-23 Add telemetry library licensing headers + fix telemetry import version
2020-04-23 Introduce wall-mountable fan holder
2020-04-23 Bump README's
2020-04-23 Fan Holder V2
2020-04-23 More Control UI code refactored
2020-04-23 Add more TODO
2020-04-23 Contributor note
2020-04-23 Badges
2020-04-23 Add dummy Control Lint workflow
2020-04-23 Test fix
2020-04-23 Control UI Cross-Compile script + notes
2020-04-23 Fixes
2020-04-23 Add websites
2020-04-23 Hacky build script for now, but works
2020-04-23 Fix?
2020-04-23 Refactor boot message
2020-04-23 Add badge links
2020-04-23 Add a 'stopped' telemetry message & add tool to record/play telemetry
2020-04-23 Use cmH2O for command pressures & fix several bugs
2020-04-23 Fix build
2020-04-23 Re-record an example
2020-04-23 added omron sensor
2020-04-24 Bump CP V2
2020-04-24 Reorg. blower
2020-04-24 Reorg. blower-holder
2020-04-24 100% done w/ CP V2
2020-04-24 Publish standalone message structs instead of one big enum
2020-04-24 Bump CP V2 render
2020-04-24 Fix CP V2 wording no2
2020-04-24 Reorg. machine-filter-box
2020-04-24 Reorg. patient-filter-box
2020-04-24 Reorg. pressure-valve
2020-04-24 Control: Update to new telemetry lib
2020-04-24 Telemetry: Derive Default for MachineStateSnapshot
    Needed to at least display default values of widgets
2020-04-24 Control: cargo fmt & clippy
2020-04-24 Add support for recorded files instead of serial port
2020-04-24 Start over when recorded file has finish playing
2020-04-24 Deploying to gh-pages from @ 97085b89ec8296f2bd2ac4f4a4d1f0b10c4d69fe 🚀
2020-04-24 Control: use systick field of messages instead of getting a local time
    All time has been switched to UTC if we ever want to manipulate it
    later. Because we do not display the date on the graph, that's ok for
    now.
2020-04-24 Fix lint
2020-04-24 Improve error message
2020-04-24 Deploying to gh-pages from @ d1205f4cf75d5ebaece27cd4979940910fe01b12 🚀
2020-04-24 Redirect from /docs/software/firmware to the documentation homepage
2020-04-24 Control: Pin to 30fps
    Also has a few performance improvements and event loop refactor
2020-04-24 reset after calibration
2020-04-25 Control: display various messages following the telemetry state
    It introduces:
    - A device disconnected or no Data received message
    - A "press start to begin" message when the makair is stopped
    - An error message when an unknown error happens
2020-04-25 Re-architecture drawer code
2020-04-25 Fix wrong extension
2020-04-25 Trigger CI
2020-04-25 testing emerson valves
2020-04-25 Code style
2020-04-25 Control: set fullscreen
2020-04-25 Telemetry: add a record from boot with fake cycles and all parameters changes
2020-04-25 Control: round boxes of data / command
2020-04-25 add pressure trigger support
2020-04-25 Control: fmt & clippy
2020-04-25 Drop widget macros
2020-04-25 Update README.md
    move badges down to be more understunable by non technical poeples
2020-04-26 Bump
2020-04-26 Add an environment offset height
2020-04-26 Add proptest for parsers.rs
2020-04-26 Refactor more rendering code
2020-04-26 Control: rework widgets
2020-04-26 Control: add a command flag to launch in fullscreen mode
2020-04-26 Control: fix widgets rebase gone wrong
    Some changes went missing
2020-04-26 Add device_id in proptest for parsers.rs
2020-04-26 Use “point_size” instead of line stroke width; fixes crashes?
2020-04-26 Add test_stopped_message_parser()
2020-04-26 Control: Use the Chip struct to have the chip state in it
    Also refactor the way we poll() the serial, this will now be easier to
    handle alarm traps
2020-04-26 Improvements on graph + general positionning
2020-04-26 Prep-up playground for branding display
2020-04-26 Fix code style
2020-04-26 Execute CI on pull requests
2020-04-26 Deploying to gh-pages from @ 83f1ebcd047a078671ef2c9adf3cebb6d9681796 🚀
2020-04-26 Fix clippies
2020-04-26 Add test_machine_state_snapshot_message_parser()
2020-04-26 Control: Add a message when device is initializing
2020-04-26 Add test_alarm_trap_message_parser()
2020-04-26 Fix indent inside proptest!{}
2020-04-26 Fix README
2020-04-27 Re-align logo
2020-04-27 Done w/ logo positioning
2020-04-27 Working logo w/ version passing
2020-04-27 Refactor + lowercase logs in telemetry lib
2020-04-27 Increase control graph size
2020-04-27 Remove a useless dependency
2020-04-27 Avoid implicit conversion
2020-04-27 Deploying to gh-pages from @ 77d6bccc59160a5c758383077e4d4105c6c77e91 🚀
2020-04-27 Add alarms box
2020-04-27 Deploying to gh-pages from @ 3ad6f28a165ff054cc38efd31e51f7378b04f1e3 🚀
2020-04-27 Fix a potential overflow
2020-04-27 Fix clippy's reports on GitHub Actions
    See https://github.com/actions-rs/clippy-check#inputs
2020-04-27 Refactor widget code
2020-04-27 Foix
2020-04-27 Re-order sponsors
2020-04-27 Telemetry: Impl Ord and PartialOrd for AlarmPriority
2020-04-27 Control: display ongoing alerts
2020-04-27 Add bl lobo
2020-04-27 Bump CP renders
2020-04-27 Control: Set Low priority alarms color
2020-04-27 Enable sonarcloud for c++ sources
2020-04-27 Remove logs during build as travis failed
    The job exceeded the maximum log length, and has been terminated.
2020-04-27 Create missing folder for analysis
2020-04-27 Add systick to machine state snapshot
2020-04-27 Fix code review
2020-04-27 Remove comment about old build tool
2020-04-27 Control: Render data screen with a stopped message when device is stopped
2020-04-27 Deploying to gh-pages from @ fc1e248dc2f4809df0ac340f7690e51f13935058 🚀
2020-04-27 improve plateau control
2020-04-27 Fix travis build
2020-04-27 Control: update alarms each time we receive a MachineStateSnapshot message
2020-04-27 Telemetry: Impl TryFrom for AlarmPriority
2020-04-27 Fix various bugs found by Sonar
2020-04-27 Add System Architecture (thanks @ejuliot)
2020-04-27 Control: Graph: render line with a stroke_width of 1
    Until https://github.com/38/plotters/issues/133 is fixed
2020-04-27 Test Chip::new_event() with any sequence of TelemetryMessage
2020-04-27 Control: update chip tick on each MachineStateSnapshot message
2020-04-28 Improve alarms management
2020-04-28 Import telemetry arrow
2020-04-28 Import telemetry arrow logo
2020-04-28 Done adding arrows
2020-04-28 Add app icon
2020-04-28 Add records
2020-04-28 add limitation to peak pressure
2020-04-28 Properly embed images and fonts in release executable
2020-04-28 Fix a clippy warning
2020-04-28 Lint
2020-04-28 first stepper low layer
2020-04-28 remove limitation for peak pressure decrease and plateau pressure increase
2020-04-28 “Heartbeat” breathing indicator soon done
2020-04-28 Finish telemetry_message_strategy()
2020-04-28 Remove unused code
2020-04-28 Deploying to gh-pages from @ 487f2e419d0e68ed06c54b03c2ef82d3e9a8a7c3 🚀
2020-04-28 Control: Chip: fix cleaning events
2020-04-28 Deploying to gh-pages from @ 5c8bb20cad9a9d1be4dde9c6a5c943c730891575 🚀
2020-04-28 Add dirty_copy_paste mod as a cargo config workaround for the moment
2020-04-28 Remove unused
2020-04-28 Telemetry: update some records
2020-04-29 Center alarms text
2020-04-29 Populated “unit active” + “ac power” sections
2020-04-29 trigger function implementation
2020-04-29 Bump Control UI
2020-04-29 Hook heartbeat indicator onto target peak pressure
2020-04-29 Fullscreen => expanded
2020-04-29 Dynamic graph maxP
2020-04-29 Deploying to gh-pages from @ f6624a94cf8a1ec60afd856bf24aef5c3fe9e586 🚀
2020-04-29 Deploying to gh-pages from @ ca3f5636baf02c856802842edf7ec0a2ef7f0ccb 🚀
2020-04-29 2.2kg.cm , 400ms achievement
2020-04-29 Add input arg
2020-04-29 Bump README
2020-04-29 Add tested Rust version
2020-04-29 Support recording from control
2020-04-29 Dim alarm container bg color if there is no alarm
2020-04-29 Fix input
2020-04-29 Add CU instructions
2020-04-29 Add France 3 coverage
2020-04-29 DYNAMIC ALARMS!!!
2020-04-29 Dynamic margin top for alarms wrapper
2020-04-29 basic sync warpscript
2020-04-29 Comment
2020-04-29 fix upload ts
2020-04-29 Control: fix TELEMETRY_POINTS_PER_SECOND constant
    DataSnapshot comes once every 10ms, not every 1ms
2020-04-29 Control: fix the peak, plateau and peep units
    I thought it was a 0..
2020-04-30 fix scale
2020-04-30 Graph auto-scale over target maximum (100% + 15% overflow allowance)
2020-04-30 Move graph y axis number of labels into env
2020-04-30 Dumb hack to fix graph left jitter point issue
2020-04-30 added auto homing and optical sync
2020-05-01 Battery power indicator OK
2020-05-01 Rebuild alarm list as to filter out ignored alarm codes
2020-05-01 Fix grammary
2020-05-01 add faulhaber motors support, first version
2020-05-01 avoid github failures
2020-05-01 latest angles for faulhaber motors
2020-05-01 Add a new pid preset for faulhaber motors
2020-05-01 close the valve more gently after inspiration, because the faulhaber is too fast
2020-05-01 Fix typos, lint and coding style
2020-05-01 Restore default configuration
2020-05-01 Fix a typo
2020-05-01 Support for unit stopped
2020-05-01 Gently close valves only with faulhaber motors
2020-05-01 Show battery level (as voltage for now)
2020-05-01 All telemetry unwrap()s become expect()s
2020-05-01 Add stateful Strategies
2020-05-01 Fix lint & coding style
2020-05-01 Use inferred lifetime
2020-05-01 Reduce visibility and remove unused code
2020-05-01 wip: Nix packaging using cargo2nix
    There are a lot of things to patch here, as building crates using nix
    has several caveats, but the C code packaged by some crates make it
    impossible to build on a NixOS system.
    That might not be a problem on the CI though
2020-05-01 Deploying to gh-pages from @ 85334a8b2fb8b2418813078dfce4406862b7923d 🚀
2020-05-01 Make control window more flexible when not in fullscreen mode
2020-05-01 develop feature
2020-05-01 Fix compiler warnings due to optional feature
2020-05-01 Control: Add a pressure target line on the graph
    Fixes https://github.com/makers-for-life/makair/issues/227
2020-05-02 Bump ver
2020-05-02 Reduce number of colors on lexan
2020-05-02 Low pass filter
2020-05-02 Clippy fix
2020-05-02 Bump vers
2020-05-02 Add GUI test
2020-05-04 Add PDF renders
2020-05-04 peep OK
2020-05-04 omron in a 25mm tunnel
2020-05-05 commit .h
2020-05-05 remove unused variables
2020-05-05 remove useless vars
2020-05-05 read analog in the main loop
2020-05-05 remove pressure from screen to add flow
2020-05-05 mean display for calib
2020-05-05 manual merge
2020-05-05 fix error in integration test
2020-05-05 Rename
2020-05-05 Bump CP
2020-05-08 Remove software from this repo
2020-05-08 Update links
2020-05-08 Clear off src/ folder (exported to each sub-repo)
2020-05-08 Revert "Clear off src/ folder (exported to each sub-repo)"
    This reverts commit 0860ec841f4ae6d55704daa5b23baae60b10e5a0.
2020-05-08 Clear ignore
2020-05-08 Rework README links (half done)
2020-05-08 Issue links
2020-05-08 Clear off Components from README
2020-05-08 Add sub-projects
2020-05-08 Improve a description
2020-05-09 Sub-Projects > Projects
2020-05-09 Add Project categories
2020-05-09 Add some newspaper refs
2020-05-15 First support for Honeywell Zephyr mass flow sensor
2020-05-15 Cleanup after Honeywell Zephyr integration
2020-05-15 less point
2020-05-15 Added error modes for Honeywell Zephyr sensor
2020-06-14 add contribuition files
2020-11-15 Update readme picture
2020-11-15 Fix typos
2020-12-04 Add Mini design
2020-12-30 HW notice
2021-01-18 added RTC and second flow meter board and doc
2021-01-18 added board photos
2021-02-14 Add Article Series
2021-02-16 Bump intro video
2021-02-17 Try restricting height a different way
2021-02-26 Rack article no 2
2021-03-01 Add article 3
2021-03-22 Add article 5
2021-03-30 Add article 6
2021-05-07 Link to makair-boards repository for small PCBs
2021-05-07 Refactor links
2021-06-17 Add misc
2021-06-17 Add links to simulator
2021-06-17 Move simulators to Misc.

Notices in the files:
parts and their libraries:
COPYRIGHT: Copyright (C) 2018 Accelerated Designs. All rights reserved
COPYRIGHT: Copyright (C) 2016 Accelerated Designs. All rights reserved
